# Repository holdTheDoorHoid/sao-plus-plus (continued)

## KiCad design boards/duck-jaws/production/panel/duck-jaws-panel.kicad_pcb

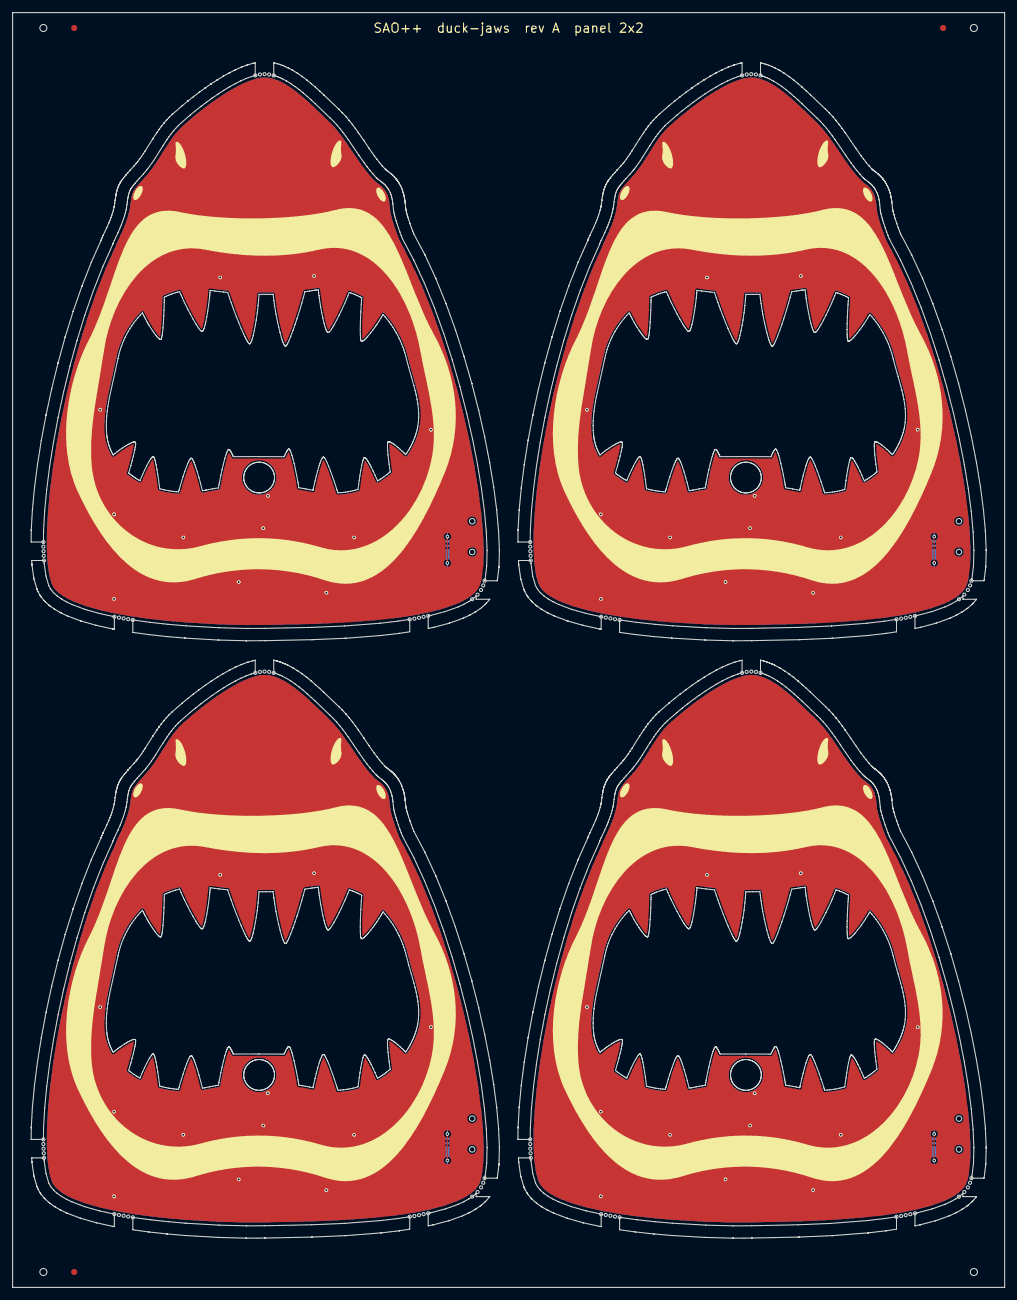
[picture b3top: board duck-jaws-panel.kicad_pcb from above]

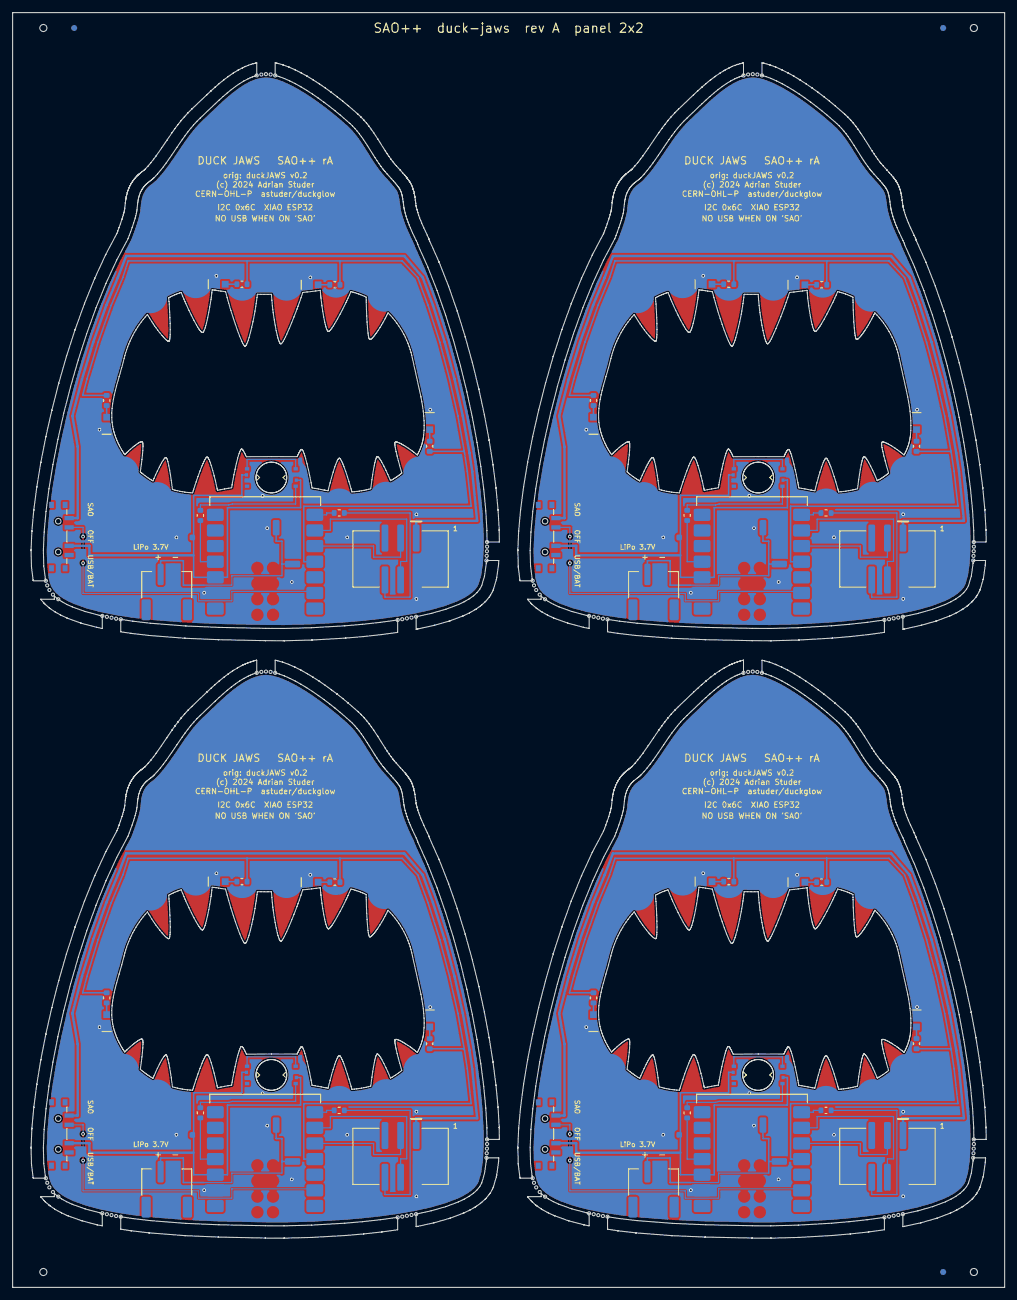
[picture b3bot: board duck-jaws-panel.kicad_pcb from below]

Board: 2 copper layers, 161.2 x 207.2 mm, 68 parts (68 on the bottom side), 68 nets.

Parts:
C101, C201, C301, C401: 100n; SAOPP_C_0603_1608Metric
D101, D102, D201, D202, D301, D302, D401, D402: SK6805-EC3210R; SAOPP_LED-20_SK6805-EC3210R_SideView_RGB
D103, D104, D105, D106, D203, D204, D205, D206, D303, D304, D305, D306, D403, D404, D405, D406: red side-firing; LED_LiteOn_LTST-S270_SideView
J101, J201, J301, J401: SAO v1.69bis; SAOPP_CONN-01_BoxHeader_2x03_P2.54mm_SMD_XFCN_BH254VS-6P
J102, J202, J302, J402: LiPo 3.7 V; SAOPP_CONN-10_JST_PH_S2B-PH-SM4-TB_1x02_Horizontal
R101, R102, R201, R202, R301, R302, R401, R402: 330; SAOPP_R_0603_1608Metric
R103, R104, R105, R106, R203, R204, R205, R206, R303, R304, R305, R306, R403, R404, R405, R406: 1.3k; SAOPP_R_0603_1608Metric
SW101, SW201, SW301, SW401: SAO / OFF / USB-BAT; SAOPP_SW-01_Slide_SP3T_CK_PCM13SMTR
U101, U201, U301, U401: XIAO ESP32-C3 / S3 / C6; SAOPP_MCU-01_Seeed_XIAO_SMD_C3_S3_C6

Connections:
B2-BAT+: J202.1, U201.15
B2-BG_A1: D203.2, R203.2
B2-BG_A2: D204.2, R204.2
B2-BG_A3: D205.2, R205.2
B2-BG_A4: D206.2, R206.2
B2-BG_DRIVE: R203.1, R204.1, R205.1, R206.1, U201.4
B2-D6_TX: R202.2, U201.7
B2-GND: C201.2, D201.1, D202.1, D203.1, D204.1, D205.1, D206.1, J201.2, J202.2, U201.13, U201.16
B2-LED_D1: D201.2, D202.3
B2-LED_DATA: R201.1, U201.11
B2-LED_DIN: D201.3, R201.2
B2-OFF_SENSE: SW201.2, U201.2
B2-SAO_GPIO2: J201.6, R202.1
B2-SCL: J201.4, U201.6
B2-SDA: J201.3, U201.5
B2-V3V3: C201.1, D201.4, D202.4, SW201.3, U201.12
B2-VSAO: J201.1, SW201.1
B3-BAT+: J302.1, U301.15
B3-BG_A1: D303.2, R303.2
B3-BG_A2: D304.2, R304.2
B3-BG_A3: D305.2, R305.2
B3-BG_A4: D306.2, R306.2
B3-BG_DRIVE: R303.1, R304.1, R305.1, R306.1, U301.4
B3-D6_TX: R302.2, U301.7
B3-GND: C301.2, D301.1, D302.1, D303.1, D304.1, D305.1, D306.1, J301.2, J302.2, U301.13, U301.16
B3-LED_D1: D301.2, D302.3
B3-LED_DATA: R301.1, U301.11
B3-LED_DIN: D301.3, R301.2
B3-OFF_SENSE: SW301.2, U301.2
B3-SAO_GPIO2: J301.6, R302.1
B3-SCL: J301.4, U301.6
B3-SDA: J301.3, U301.5
B3-V3V3: C301.1, D301.4, D302.4, SW301.3, U301.12
B3-VSAO: J301.1, SW301.1
B4-BAT+: J402.1, U401.15
B4-BG_A1: D403.2, R403.2
B4-BG_A2: D404.2, R404.2
B4-BG_A3: D405.2, R405.2
B4-BG_A4: D406.2, R406.2
B4-BG_DRIVE: R403.1, R404.1, R405.1, R406.1, U401.4
B4-D6_TX: R402.2, U401.7
B4-GND: C401.2, D401.1, D402.1, D403.1, D404.1, D405.1, D406.1, J401.2, J402.2, U401.13, U401.16
B4-LED_D1: D401.2, D402.3
B4-LED_DATA: R401.1, U401.11
B4-LED_DIN: D401.3, R401.2
B4-OFF_SENSE: SW401.2, U401.2
B4-SAO_GPIO2: J401.6, R402.1
B4-SCL: J401.4, U401.6
B4-SDA: J401.3, U401.5
B4-V3V3: C401.1, D401.4, D402.4, SW401.3, U401.12
B4-VSAO: J401.1, SW401.1
BAT+: J102.1, U101.15
BG_A1: D103.2, R103.2
BG_A2: D104.2, R104.2
BG_A3: D105.2, R105.2
BG_A4: D106.2, R106.2
BG_DRIVE: R103.1, R104.1, R105.1, R106.1, U101.4
D6_TX: R102.2, U101.7
GND: C101.2, D101.1, D102.1, D103.1, D104.1, D105.1, D106.1, J101.2, J102.2, U101.13, U101.16
LED_D1: D101.2, D102.3
LED_DATA: R101.1, U101.11
LED_DIN: D101.3, R101.2
OFF_SENSE: SW101.2, U101.2
SAO_GPIO2: J101.6, R102.1
SCL: J101.4, U101.6
SDA: J101.3, U101.5
V3V3: C101.1, D101.4, D102.4, SW101.3, U101.12
VSAO: J101.1, SW101.1

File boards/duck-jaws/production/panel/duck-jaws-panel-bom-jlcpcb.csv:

Comment,Designator,Footprint,LCSC Part #
100n,"C101,C201,C301,C401",SAOPP_C_0603_1608Metric,C14663
SK6805-EC3210R,"D101,D102,D201,D202,D301,D302,D401,D402",SAOPP_LED-20_SK6805-EC3210R_SideView_RGB,C5378735
red side-firing,"D103,D104,D105,D106,D203,D204,D205,D206,D303,D304,D305,D306,D403,D404,D405,D406",LED_LiteOn_LTST-S270_SideView,C125114
SAO v1.69bis,"J101,J201,J301,J401",SAOPP_CONN-01_BoxHeader_2x03_P2.54mm_SMD_XFCN_BH254VS-6P,C492445
LiPo 3.7 V,"J102,J202,J302,J402",SAOPP_CONN-10_JST_PH_S2B-PH-SM4-TB_1x02_Horizontal,C295747
330,"R101,R102,R201,R202,R301,R302,R401,R402",SAOPP_R_0603_1608Metric,C23138
1.3k,"R103,R104,R105,R106,R203,R204,R205,R206,R303,R304,R305,R306,R403,R404,R405,R406",SAOPP_R_0603_1608Metric,C22767
SAO / OFF / USB-BAT,"SW101,SW201,SW301,SW401",SAOPP_SW-01_Slide_SP3T_CK_PCM13SMTR,C221842
XIAO ESP32-C3 / S3 / C6,"U101,U201,U301,U401",SAOPP_MCU-01_Seeed_XIAO_SMD_C3_S3_C6,

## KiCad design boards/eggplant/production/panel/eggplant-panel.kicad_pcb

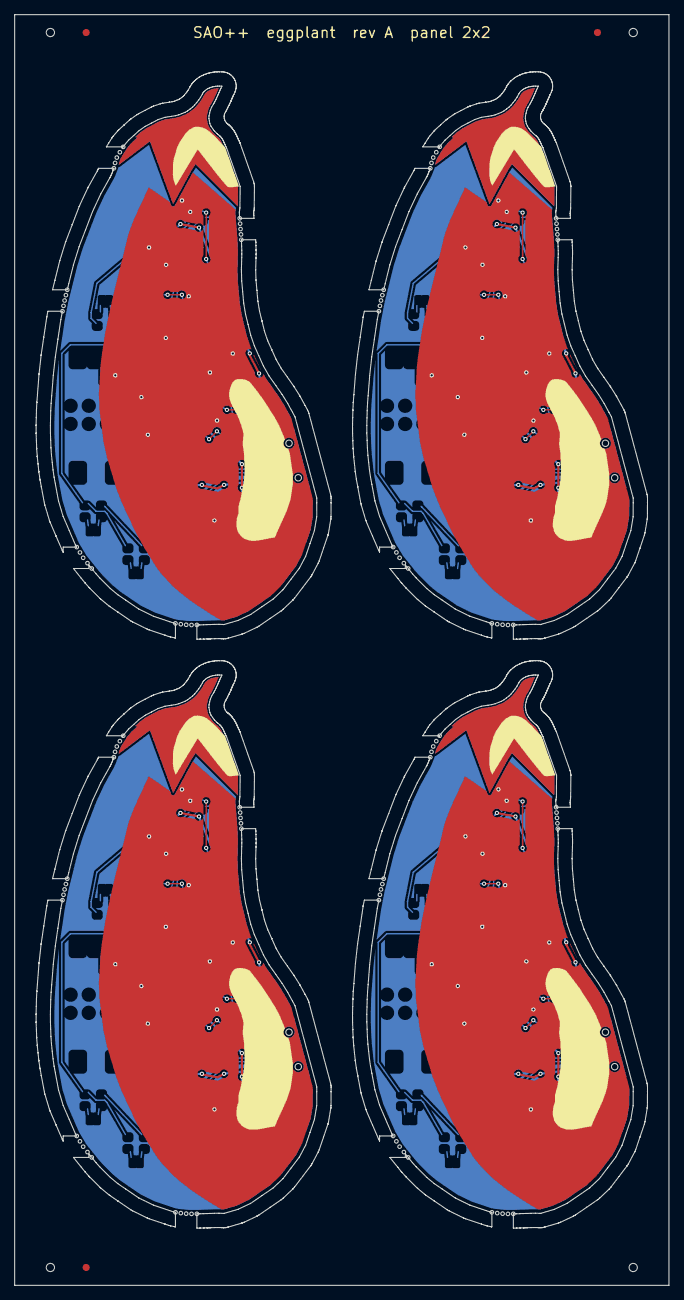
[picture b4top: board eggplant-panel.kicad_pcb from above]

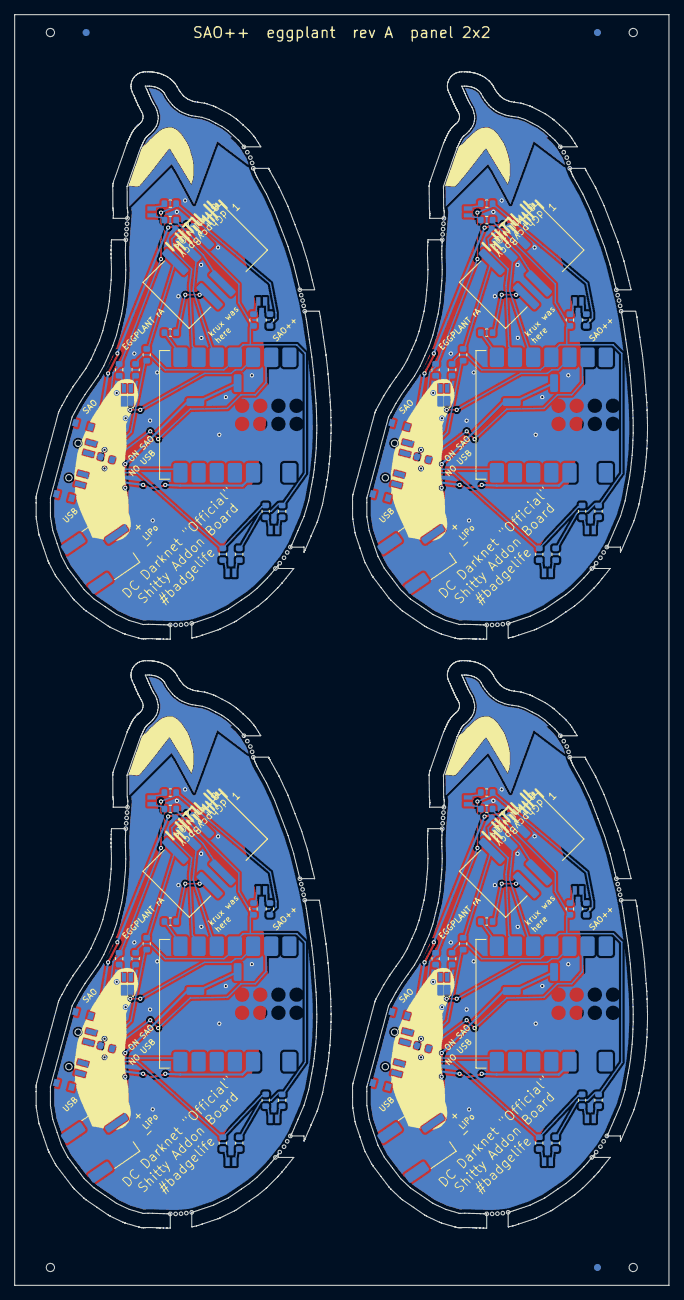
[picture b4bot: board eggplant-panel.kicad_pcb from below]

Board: 2 copper layers, 91.6 x 177.8 mm, 88 parts (88 on the bottom side), 96 nets.

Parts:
D101, D102, D103, D104, D105, D201, D202, D203, D204, D205, D301, D302, D303, D304, D305, D401, D402, D403, D404, D405: blue/red; LED_Bicolour_0805
J101, J201, J301, J401: SAO v1.69bis; SAOPP_CONN-01_BoxHeader_2x03_P2.54mm_SMD_XFCN_BH254VS-6P
J102, J202, J302, J402: LiPo 3.7 V; SAOPP_CONN-10_JST_PH_S2B-PH-SM4-TB_1x02_Horizontal
R101, R102, R103, R104, R105, R106, R107, R108, R201, R202, R203, R204, R205, R206, R207, R208, R301, R302, R303, R304, R305, R306, R307, R308, R401, R402, R403, R404, R405, R406, R407, R408: 330; SAOPP_R_0603_1608Metric
R109, R110, R111, R112, R113, R209, R210, R211, R212, R213, R309, R310, R311, R312, R313, R409, R410, R411, R412, R413: 1.3k; SAOPP_R_0603_1608Metric
SW101, SW201, SW301, SW401: SAO / OFF / USB-BAT; SAOPP_SW-01_Slide_SP3T_CK_PCM13SMTR
U101, U201, U301, U401: XIAO ESP32-C3 / S3 / C6; SAOPP_MCU-01_Seeed_XIAO_SMD_C3_S3_C6

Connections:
B2-BAT+: J202.1, U201.15
B2-BLUE1: D201.1, R204.2
B2-BLUE2: D202.1, R205.2
B2-BLUE3: D203.1, R206.2
B2-BLUE4: D204.1, R207.2
B2-BLUE5: D205.1, R208.2
B2-D6_TX: R203.2, U201.7
B2-D7_RX: R202.2, U201.8
B2-GND: D201.3, D201.4, D202.3, D202.4, D203.3, D203.4, D204.3, D204.4, D205.3, D205.4, J201.2, J202.2, U201.13, U201.16
B2-LED_BLUE: R204.1, R205.1, R206.1, R207.1, R208.1, U201.4
B2-LED_RED: R209.1, R210.1, R211.1, R212.1, R213.1, U201.3
B2-OFF_SENSE: R201.2, U201.2
B2-OFF_SW: R201.1, SW201.2
B2-RED1: D201.2, R209.2
B2-RED2: D202.2, R210.2
B2-RED3: D203.2, R211.2
B2-RED4: D204.2, R212.2
B2-RED5: D205.2, R213.2
B2-SAO_GPIO1: J201.5, R202.1
B2-SAO_GPIO2: J201.6, R203.1
B2-SCL: J201.4, U201.6
B2-SDA: J201.3, U201.5
B2-V3V3: SW201.3, U201.12
B2-VSAO: J201.1, SW201.1
B3-BAT+: J302.1, U301.15
B3-BLUE1: D301.1, R304.2
B3-BLUE2: D302.1, R305.2
B3-BLUE3: D303.1, R306.2
B3-BLUE4: D304.1, R307.2
B3-BLUE5: D305.1, R308.2
B3-D6_TX: R303.2, U301.7
B3-D7_RX: R302.2, U301.8
B3-GND: D301.3, D301.4, D302.3, D302.4, D303.3, D303.4, D304.3, D304.4, D305.3, D305.4, J301.2, J302.2, U301.13, U301.16
B3-LED_BLUE: R304.1, R305.1, R306.1, R307.1, R308.1, U301.4
B3-LED_RED: R309.1, R310.1, R311.1, R312.1, R313.1, U301.3
B3-OFF_SENSE: R301.2, U301.2
B3-OFF_SW: R301.1, SW301.2
B3-RED1: D301.2, R309.2
B3-RED2: D302.2, R310.2
B3-RED3: D303.2, R311.2
B3-RED4: D304.2, R312.2
B3-RED5: D305.2, R313.2
B3-SAO_GPIO1: J301.5, R302.1
B3-SAO_GPIO2: J301.6, R303.1
B3-SCL: J301.4, U301.6
B3-SDA: J301.3, U301.5
B3-V3V3: SW301.3, U301.12
B3-VSAO: J301.1, SW301.1
B4-BAT+: J402.1, U401.15
B4-BLUE1: D401.1, R404.2
B4-BLUE2: D402.1, R405.2
B4-BLUE3: D403.1, R406.2
B4-BLUE4: D404.1, R407.2
B4-BLUE5: D405.1, R408.2
B4-D6_TX: R403.2, U401.7
B4-D7_RX: R402.2, U401.8
B4-GND: D401.3, D401.4, D402.3, D402.4, D403.3, D403.4, D404.3, D404.4, D405.3, D405.4, J401.2, J402.2, U401.13, U401.16
B4-LED_BLUE: R404.1, R405.1, R406.1, R407.1, R408.1, U401.4
B4-LED_RED: R409.1, R410.1, R411.1, R412.1, R413.1, U401.3
B4-OFF_SENSE: R401.2, U401.2
B4-OFF_SW: R401.1, SW401.2
B4-RED1: D401.2, R409.2
B4-RED2: D402.2, R410.2
B4-RED3: D403.2, R411.2
B4-RED4: D404.2, R412.2
B4-RED5: D405.2, R413.2
B4-SAO_GPIO1: J401.5, R402.1
B4-SAO_GPIO2: J401.6, R403.1
B4-SCL: J401.4, U401.6
B4-SDA: J401.3, U401.5
B4-V3V3: SW401.3, U401.12
B4-VSAO: J401.1, SW401.1
BAT+: J102.1, U101.15
BLUE1: D101.1, R104.2
BLUE2: D102.1, R105.2
BLUE3: D103.1, R106.2
BLUE4: D104.1, R107.2
BLUE5: D105.1, R108.2
D6_TX: R103.2, U101.7
D7_RX: R102.2, U101.8
GND: D101.3, D101.4, D102.3, D102.4, D103.3, D103.4, D104.3, D104.4, D105.3, D105.4, J101.2, J102.2, U101.13, U101.16
LED_BLUE: R104.1, R105.1, R106.1, R107.1, R108.1, U101.4
LED_RED: R109.1, R110.1, R111.1, R112.1, R113.1, U101.3
OFF_SENSE: R101.2, U101.2
OFF_SW: R101.1, SW101.2
RED1: D101.2, R109.2
RED2: D102.2, R110.2
RED3: D103.2, R111.2
RED4: D104.2, R112.2
RED5: D105.2, R113.2
SAO_GPIO1: J101.5, R102.1
SAO_GPIO2: J101.6, R103.1
SCL: J101.4, U101.6
SDA: J101.3, U101.5
V3V3: SW101.3, U101.12
VSAO: J101.1, SW101.1

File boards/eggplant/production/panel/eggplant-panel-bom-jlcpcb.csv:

Comment,Designator,Footprint,LCSC Part #
blue/red,"D101,D102,D103,D104,D105,D201,D202,D203,D204,D205,D301,D302,D303,D304,D305,D401,D402,D403,D404,D405",LED_Bicolour_0805,C5568785
SAO v1.69bis,"J101,J201,J301,J401",SAOPP_CONN-01_BoxHeader_2x03_P2.54mm_SMD_XFCN_BH254VS-6P,C492445
LiPo 3.7 V,"J102,J202,J302,J402",SAOPP_CONN-10_JST_PH_S2B-PH-SM4-TB_1x02_Horizontal,C295747
330,"R101,R102,R103,R104,R105,R106,R107,R108,R201,R202,R203,R204,R205,R206,R207,R208,R301,R302,R303,R304,R305,R306,R307,R308,R401,R402,R403,R404,R405,R406,R407,R408",SAOPP_R_0603_1608Metric,C23138
1.3k,"R109,R110,R111,R112,R113,R209,R210,R211,R212,R213,R309,R310,R311,R312,R313,R409,R410,R411,R412,R413",SAOPP_R_0603_1608Metric,C22767
SAO / OFF / USB-BAT,"SW101,SW201,SW301,SW401",SAOPP_SW-01_Slide_SP3T_CK_PCM13SMTR,C221842
XIAO ESP32-C3 / S3 / C6,"U101,U201,U301,U401",SAOPP_MCU-01_Seeed_XIAO_SMD_C3_S3_C6,

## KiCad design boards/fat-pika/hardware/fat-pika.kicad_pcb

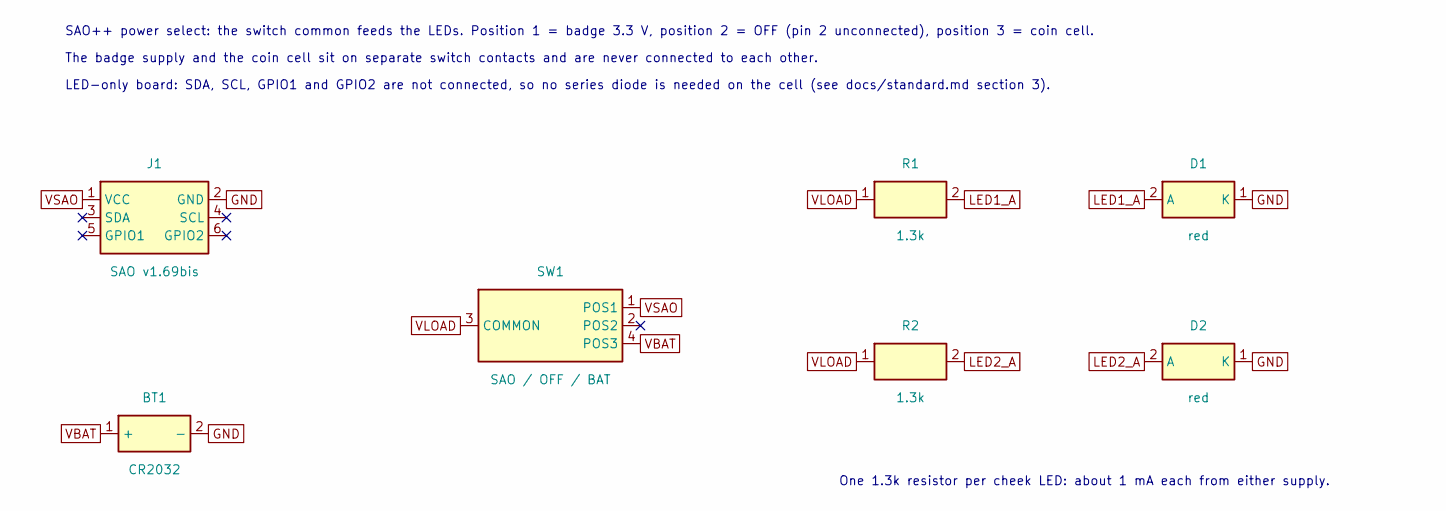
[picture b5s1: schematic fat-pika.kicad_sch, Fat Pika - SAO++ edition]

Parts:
BT1: CR2032; SAOPP_BAT-01_CR2032_SMD_TE_BAT-HLD-001; MPN BAT-HLD-001; LCSC C7501066
D1, D2: red; SAOPP_LED-10_1206_ReverseMount_ThroughBoard; MPN LTST-C230KRKT; LCSC C125107
J1: SAO v1.69bis; SAOPP_CONN-01_BoxHeader_2x03_P2.54mm_SMD_XFCN_BH254VS-6P; MPN BH254VS-6P; LCSC C492445
R1, R2: 1.3k; SAOPP_R_0603_1608Metric; MPN 0603 1.3k 1%
SW1: SAO / OFF / BAT; SAOPP_SW-01_Slide_SP3T_CK_PCM13SMTR; MPN PCM13SMTR; LCSC C221842

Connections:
GND: BT1.2 (-), D1.1 (K), D2.1 (K), J1.2 (GND)
LED1_A: D1.2 (A), R1.2
LED2_A: D2.2 (A), R2.2
VBAT: BT1.1 (+), SW1.4 (POS3)
VLOAD: R1.1, R2.1, SW1.3 (COMMON)
VSAO: J1.1 (VCC), SW1.1 (POS1)

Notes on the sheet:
SAO++ power select: the switch common feeds the LEDs. Position 1 = badge 3.3 V, position 2 = OFF (pin 2 unconnected), position 3 = coin cell.
The badge supply and the coin cell sit on separate switch contacts and are never connected to each other.
LED-only board: SDA, SCL, GPIO1 and GPIO2 are not connected, so no series diode is needed on the cell (see docs/standard.md section 3).
One 1.3k resistor per cheek LED: about 1 mA each from either supply.

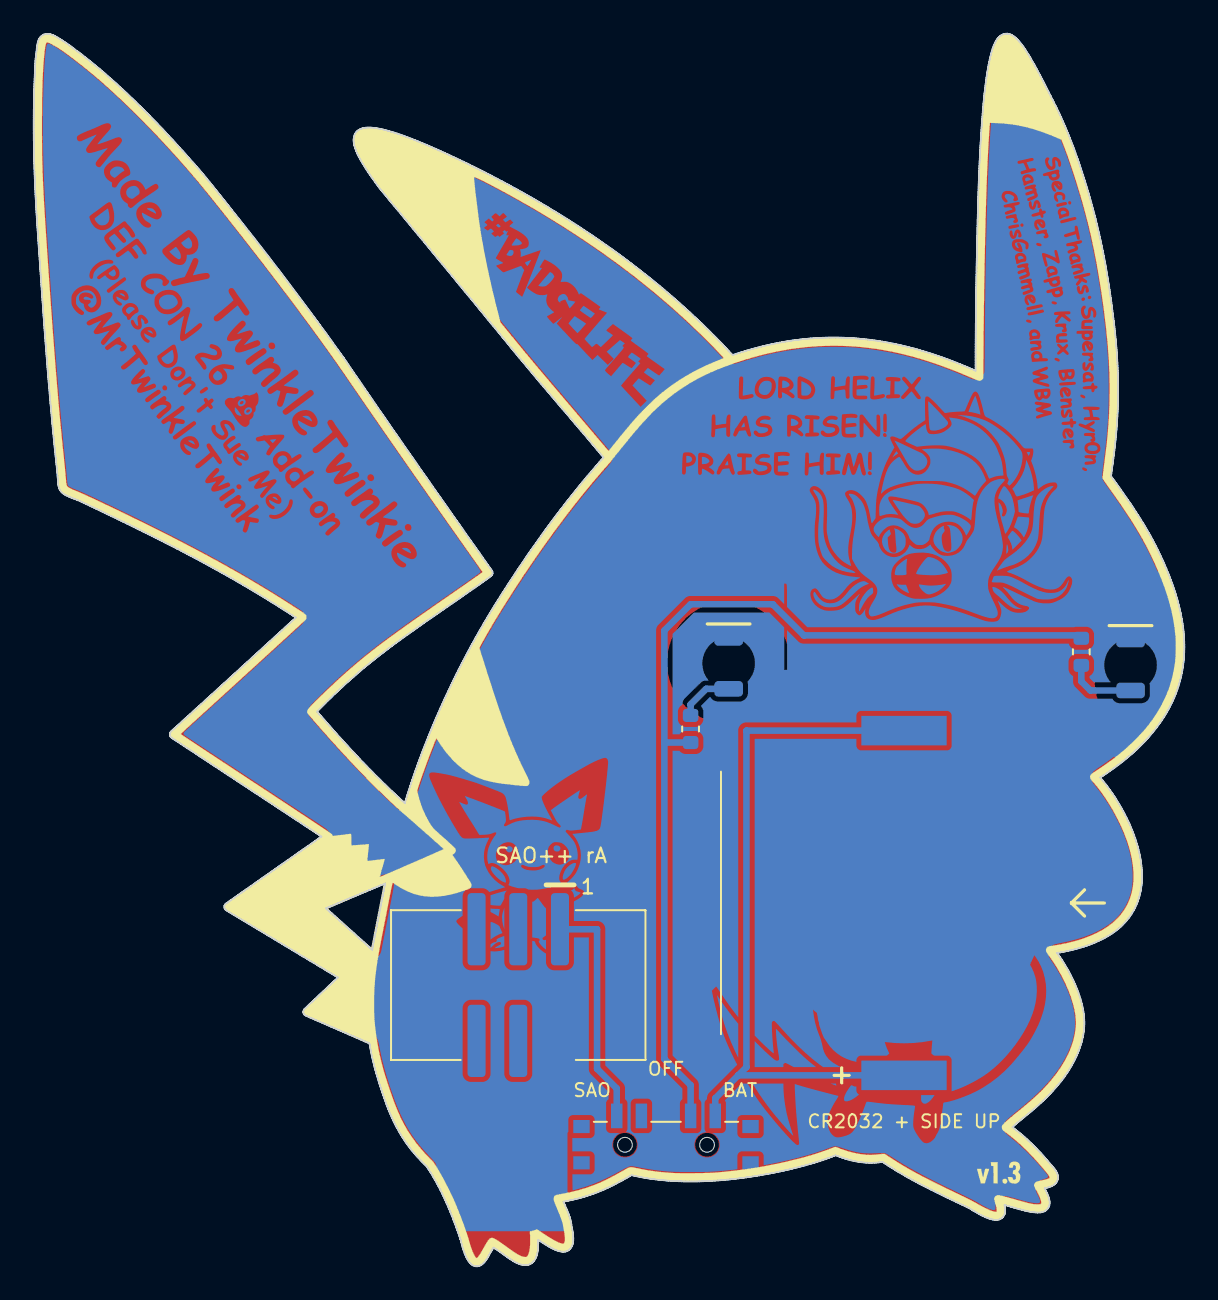
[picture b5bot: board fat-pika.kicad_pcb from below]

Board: 2 copper layers, 70.1 x 75.1 mm, 12 parts (7 on the bottom side), 6 nets.

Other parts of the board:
B.Cu: LOGO; B.Cu_g5770
B.Silk: LOGO
F.Cu: LOGO; F.Cu_g5776
F.Mask, F.Silk: LOGO

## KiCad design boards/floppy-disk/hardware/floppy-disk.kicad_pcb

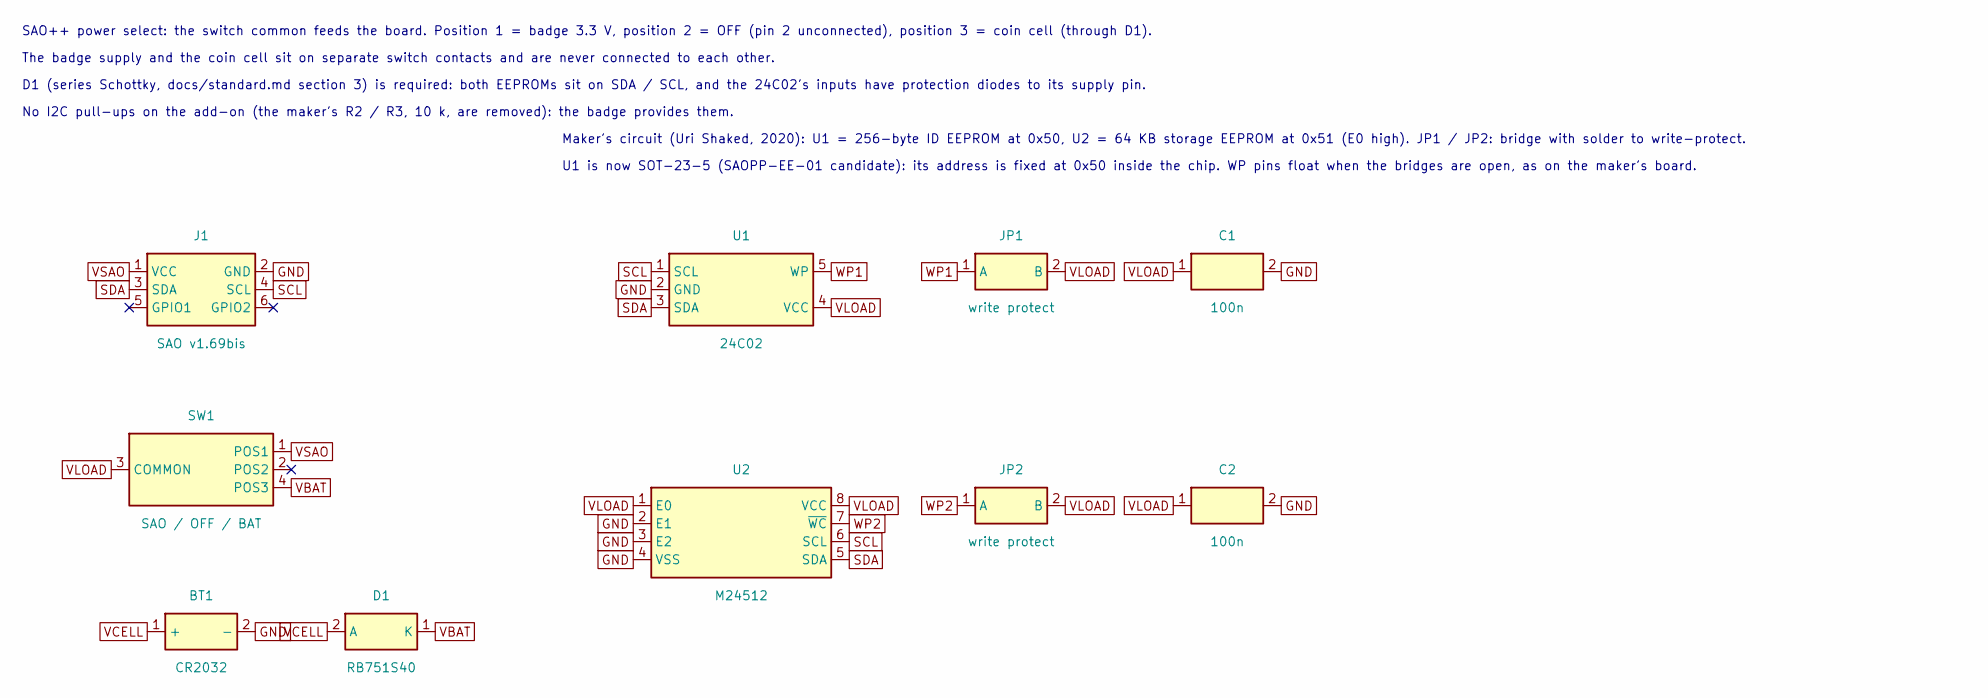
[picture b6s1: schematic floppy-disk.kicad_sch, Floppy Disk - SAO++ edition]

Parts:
BT1: CR2032; SAOPP_BAT-01_CR2032_SMD_TE_BAT-HLD-001; MPN BAT-HLD-001; LCSC C7501066
C1, C2: 100n; SAOPP_C_0603_1608Metric; MPN CC0603KRX7R9BB104; LCSC C14663
D1: RB751S40; D_SOD-523; MPN RB751S40T1G; LCSC C232576
J1: SAO v1.69bis; SAOPP_CONN-01_BoxHeader_2x03_P2.54mm_SMD_XFCN_BH254VS-6P; MPN BH254VS-6P; LCSC C492445
JP1, JP2: write protect; SolderJumper-2_P1.3mm_Open_RoundedPad1.0x1.5mm; MPN none: PCB copper, nothing fitted
SW1: SAO / OFF / BAT; SAOPP_SW-01_Slide_SP3T_CK_PCM13SMTR; MPN PCM13SMTR; LCSC C221842
U1: 24C02; SOT-23-5; MPN AD24C02; LCSC C5125083
U2: M24512; SOIC-8_3.9x4.9mm_P1.27mm; MPN M24512-RMN6TP; LCSC C79991

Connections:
GND: BT1.2 (-), C1.2, C2.2, J1.2 (GND), U1.2 (GND), U2.2 (E1), U2.3 (E2), U2.4 (VSS)
SCL: J1.4 (SCL), U1.1 (SCL), U2.6 (SCL)
SDA: J1.3 (SDA), U1.3 (SDA), U2.5 (SDA)
VBAT: D1.1 (K), SW1.4 (POS3)
VCELL: BT1.1 (+), D1.2 (A)
VLOAD: C1.1, C2.1, JP1.2 (B), JP2.2 (B), SW1.3 (COMMON), U1.4 (VCC), U2.1 (E0), U2.8 (VCC)
VSAO: J1.1 (VCC), SW1.1 (POS1)
WP1: JP1.1 (A), U1.5 (WP)
WP2: JP2.1 (A), U2.7 (~WC)

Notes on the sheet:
SAO++ power select: the switch common feeds the board. Position 1 = badge 3.3 V, position 2 = OFF (pin 2 unconnected), position 3 = coin cell (through D1).
The badge supply and the coin cell sit on separate switch contacts and are never connected to each other.
D1 (series Schottky, docs/standard.md section 3) is required: both EEPROMs sit on SDA / SCL, and the 24C02's inputs have protection diodes to its supply pin.
No I2C pull-ups on the add-on (the maker's R2 / R3, 10 k, are removed): the badge provides them.
Maker's circuit (Uri Shaked, 2020): U1 = 256-byte ID EEPROM at 0x50, U2 = 64 KB storage EEPROM at 0x51 (E0 high). JP1 / JP2: bridge with solder to write-protect.
U1 is now SOT-23-5 (SAOPP-EE-01 candidate): its address is fixed at 0x50 inside the chip. WP pins float when the bridges are open, as on the maker's board.

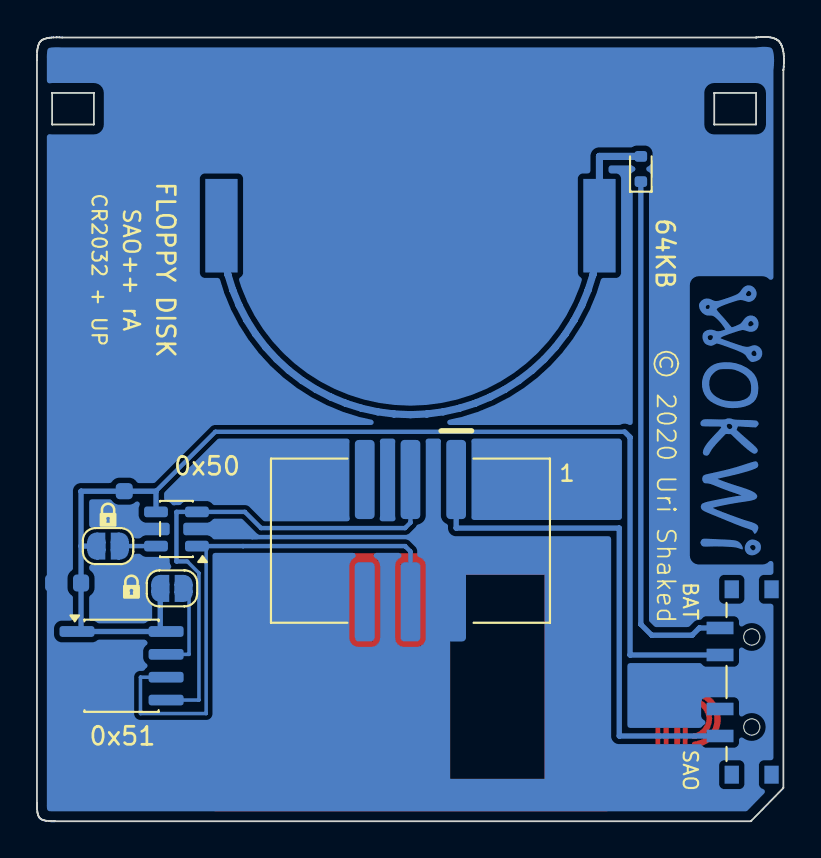
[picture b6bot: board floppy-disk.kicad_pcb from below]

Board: 2 copper layers, 41.5 x 43.6 mm, 10 parts (10 on the bottom side), 9 nets.

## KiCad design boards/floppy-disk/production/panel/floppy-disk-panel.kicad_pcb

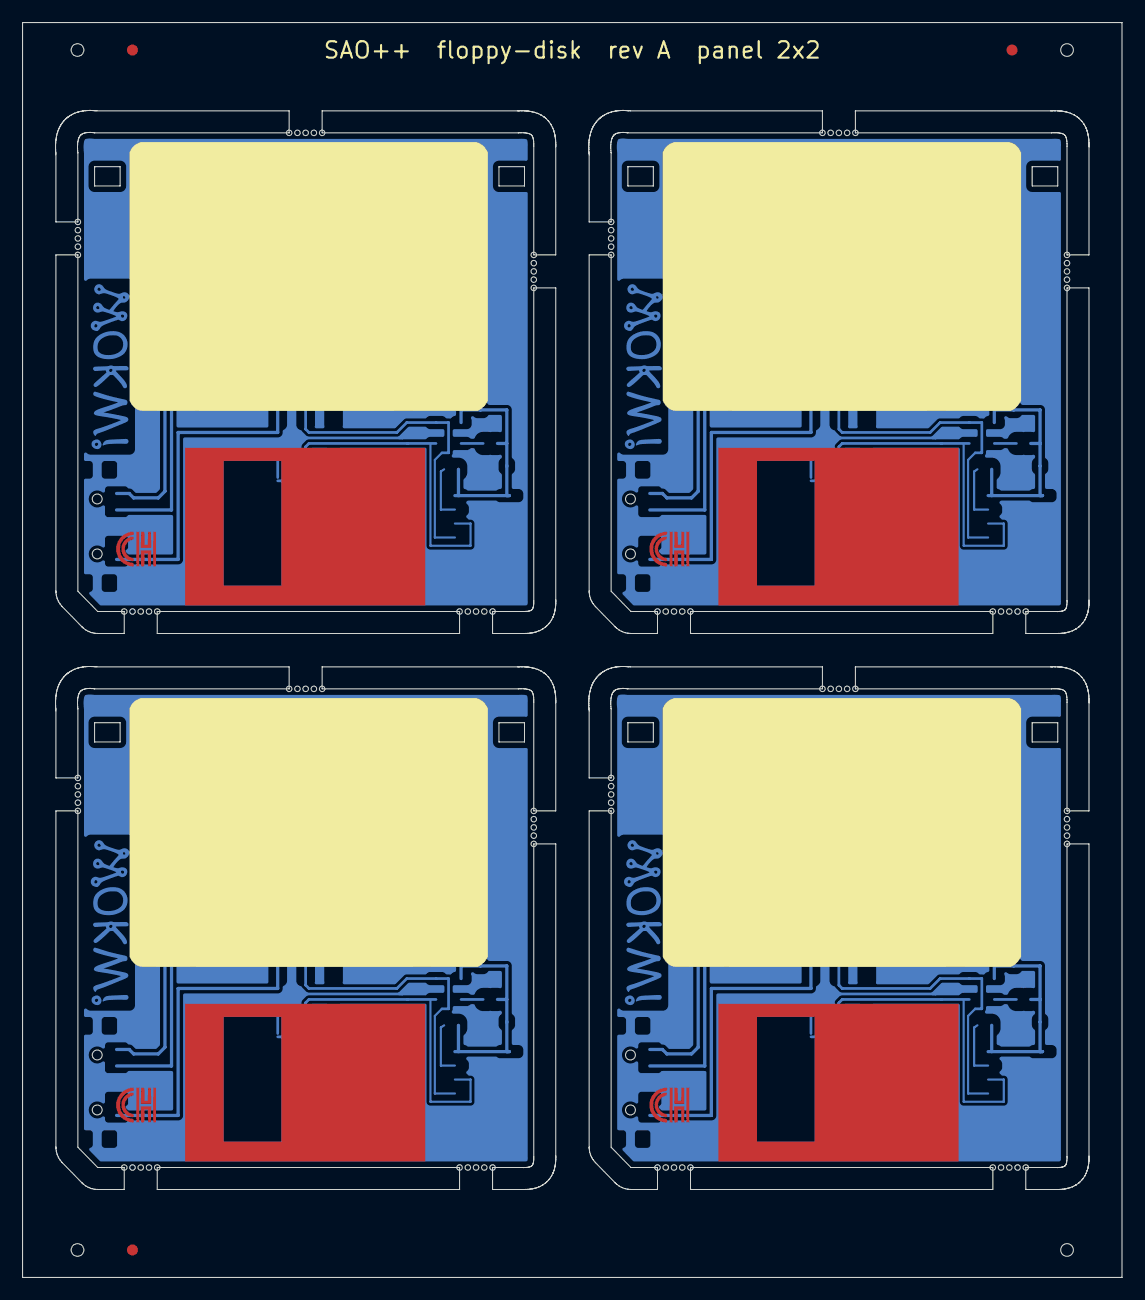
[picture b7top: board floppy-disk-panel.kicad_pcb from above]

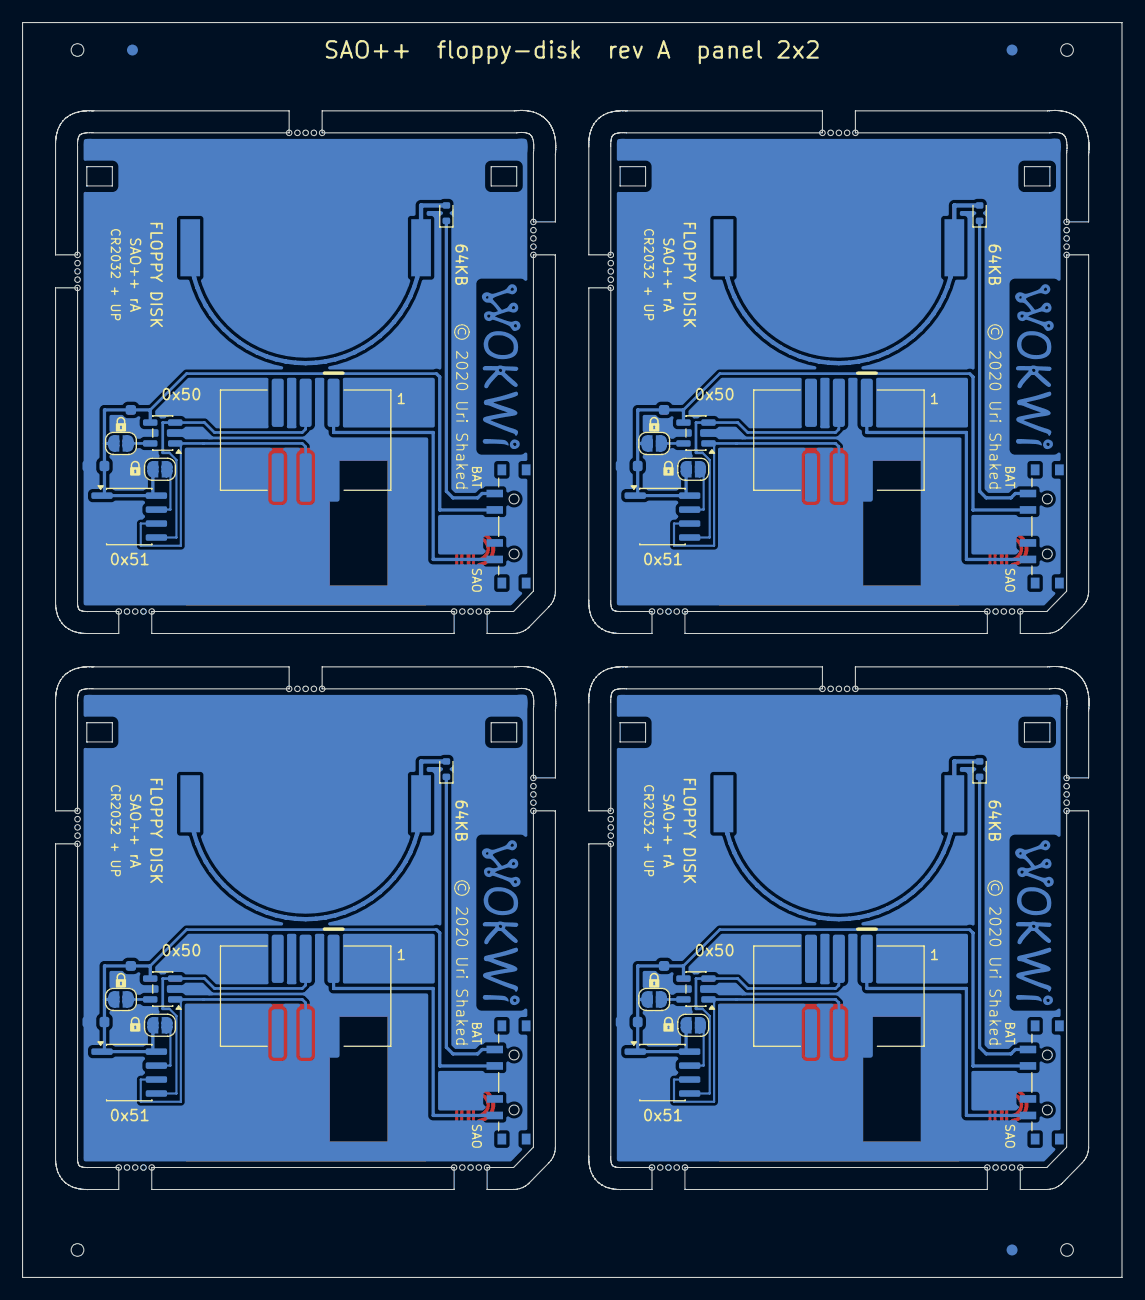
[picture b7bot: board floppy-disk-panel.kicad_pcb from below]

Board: 2 copper layers, 100.0 x 114.2 mm, 40 parts (40 on the bottom side), 36 nets.

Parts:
BT101, BT201, BT301, BT401: CR2032; SAOPP_BAT-01_CR2032_SMD_TE_BAT-HLD-001
C101, C102, C201, C202, C301, C302, C401, C402: 100n; SAOPP_C_0603_1608Metric
D101, D201, D301, D401: RB751S40; D_SOD-523
J101, J201, J301, J401: SAO v1.69bis; SAOPP_CONN-01_BoxHeader_2x03_P2.54mm_SMD_XFCN_BH254VS-6P
JP101, JP102, JP201, JP202, JP301, JP302, JP401, JP402: write protect; SolderJumper-2_P1.3mm_Open_RoundedPad1.0x1.5mm
SW101, SW201, SW301, SW401: SAO / OFF / BAT; SAOPP_SW-01_Slide_SP3T_CK_PCM13SMTR
U101, U201, U301, U401: 24C02; SOT-23-5
U102, U202, U302, U402: M24512; SOIC-8_3.9x4.9mm_P1.27mm

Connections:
B2-GND: BT201.2, C201.2, C202.2, J201.2, U201.2, U202.2, U202.3, U202.4
B2-SCL: J201.4, U201.1, U202.6
B2-SDA: J201.3, U201.3, U202.5
B2-VBAT: D201.1, SW201.4
B2-VCELL: BT201.1, D201.2
B2-VLOAD: C201.1, C202.1, JP201.2, JP202.2, SW201.3, U201.4, U202.1, U202.8
B2-VSAO: J201.1, SW201.1
B2-WP1: JP201.1, U201.5
B2-WP2: JP202.1, U202.7
B3-GND: BT301.2, C301.2, C302.2, J301.2, U301.2, U302.2, U302.3, U302.4
B3-SCL: J301.4, U301.1, U302.6
B3-SDA: J301.3, U301.3, U302.5
B3-VBAT: D301.1, SW301.4
B3-VCELL: BT301.1, D301.2
B3-VLOAD: C301.1, C302.1, JP301.2, JP302.2, SW301.3, U301.4, U302.1, U302.8
B3-VSAO: J301.1, SW301.1
B3-WP1: JP301.1, U301.5
B3-WP2: JP302.1, U302.7
B4-GND: BT401.2, C401.2, C402.2, J401.2, U401.2, U402.2, U402.3, U402.4
B4-SCL: J401.4, U401.1, U402.6
B4-SDA: J401.3, U401.3, U402.5
B4-VBAT: D401.1, SW401.4
B4-VCELL: BT401.1, D401.2
B4-VLOAD: C401.1, C402.1, JP401.2, JP402.2, SW401.3, U401.4, U402.1, U402.8
B4-VSAO: J401.1, SW401.1
B4-WP1: JP401.1, U401.5
B4-WP2: JP402.1, U402.7
GND: BT101.2, C101.2, C102.2, J101.2, U101.2, U102.2, U102.3, U102.4
SCL: J101.4, U101.1, U102.6
SDA: J101.3, U101.3, U102.5
VBAT: D101.1, SW101.4
VCELL: BT101.1, D101.2
VLOAD: C101.1, C102.1, JP101.2, JP102.2, SW101.3, U101.4, U102.1, U102.8
VSAO: J101.1, SW101.1
WP1: JP101.1, U101.5
WP2: JP102.1, U102.7

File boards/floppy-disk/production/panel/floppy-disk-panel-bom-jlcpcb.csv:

Comment,Designator,Footprint,LCSC Part #
CR2032,"BT101,BT201,BT301,BT401",SAOPP_BAT-01_CR2032_SMD_TE_BAT-HLD-001,C7501066
100n,"C101,C102,C201,C202,C301,C302,C401,C402",SAOPP_C_0603_1608Metric,C14663
RB751S40,"D101,D201,D301,D401",D_SOD-523,C232576
SAO v1.69bis,"J101,J201,J301,J401",SAOPP_CONN-01_BoxHeader_2x03_P2.54mm_SMD_XFCN_BH254VS-6P,C492445
SAO / OFF / BAT,"SW101,SW201,SW301,SW401",SAOPP_SW-01_Slide_SP3T_CK_PCM13SMTR,C221842
24C02,"U101,U201,U301,U401",SOT-23-5,C5125083
M24512,"U102,U202,U302,U402",SOIC-8_3.9x4.9mm_P1.27mm,C79991
